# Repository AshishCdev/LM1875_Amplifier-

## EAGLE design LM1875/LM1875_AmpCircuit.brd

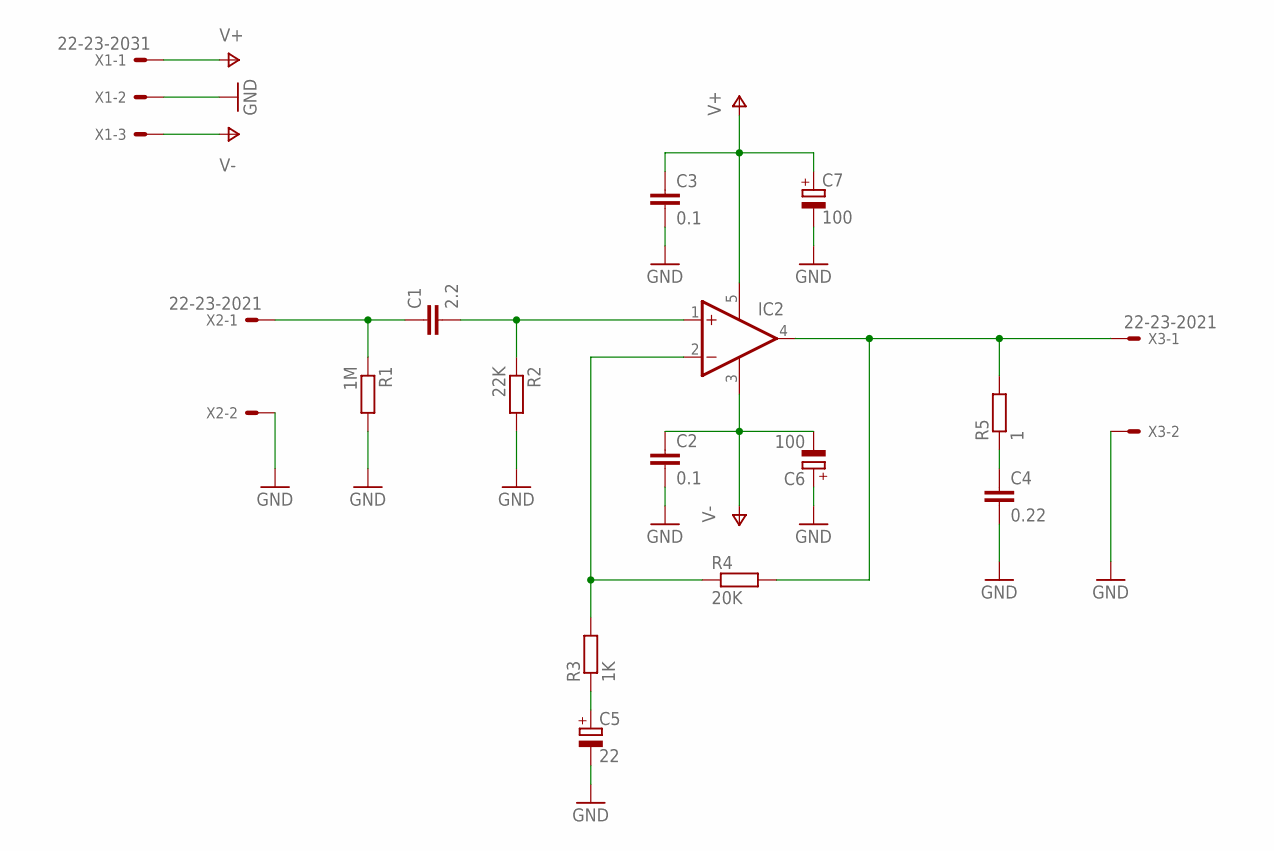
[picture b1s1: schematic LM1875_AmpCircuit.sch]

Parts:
C1: 2.2; C050-024X044
C2, C3: 0.1; C050-024X044
C4: 0.22; C050-024X044
C5: 22; E3,5-10
C6, C7: 100; E3,5-10
IC2: LM1875TO220-5; CB360
R1: 1M; 0204/7
R2: 22K; 0204/7
R3: 1K; 0204/7
R4: 20K; 0204/7
R5: 1; 0204/7
X1: 22-23-2031
X2, X3: 22-23-2021

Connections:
GND: C2.2, C3.2, C4.2, C5.-, C6.+, C7.-, R1.2, R2.2, X1.2, X2.2, X3.2
unnamed: C1.1, R1.1, X2.1
unnamed: C1.2, IC2.1 (+IN), R2.1
unnamed: C5.+, R3.1
unnamed: IC2.2 (-IN), R3.2, R4.1
unnamed: IC2.4 (OUT), R4.2, R5.2, X3.1
unnamed: C4.1, R5.1
V+: C3.1, C7.+, IC2.5 (V+), X1.1
V-: C2.1, C6.-, IC2.3 (V-), X1.3

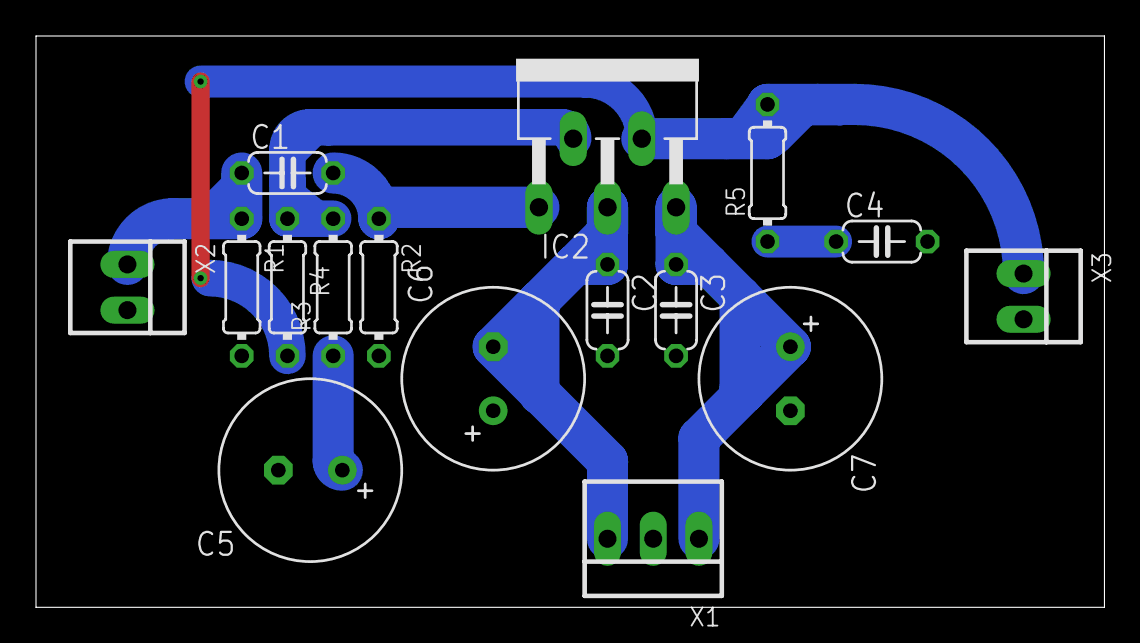
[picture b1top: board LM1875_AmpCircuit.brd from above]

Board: 2 copper layers, 59.4 x 31.7 mm, 16 parts (0 on the bottom side), 9 nets.

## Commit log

2018-10-31 Added project files for amplifier LM1875.
2018-10-31 Edited the layout for better noise rejection
